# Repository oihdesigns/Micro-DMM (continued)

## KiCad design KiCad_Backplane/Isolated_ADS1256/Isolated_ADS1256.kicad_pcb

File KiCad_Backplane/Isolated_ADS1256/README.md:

# Isolated ADS1256 — rev A

This is an isolated 24-bit ADC board, 95 × 62 mm with 4 layers. The ADS1256, its reference, clock and LDOs all sit on the isolated side. SPI crosses a TI ISO7762 (5 kVrms reinforced, 4 forward / 2 reverse channels). Power crosses a Murata MEJ1S0509SC (5 V in, 9 V out, 5.2 kVDC rated, 3 pF isolation capacitance).

Status: generated, routed and checked: ERC 0, DRC 0 at all severities, 0 unconnected, schematic parity 0. It has not been ordered or tested on hardware.

## Channels

| ADS1256 inputs | Function | Scaling | Suggested setup |
|---|---|---|---|
| AIN0 / AIN1 | ±250 VDC differential | Each leg is 3 × 825k + 10k, returned to COM. k = 10k / 2.485 MΩ = 1/248.5, so 250 V gives 1.006 V. **Vin = Vdiff × 248.5** | BUFEN = 1, PGA 4: ±1.25 V full scale = ±310 V |
| AIN2 / AIN3 | 0.1 Ω shunt (RS1, TLMQ2HDR10FTE, 1.5 W) | Kelvin taps through 100 Ω, with 10 nF C0G across the pair. **I = Vdiff / 0.1** | PGA 8: ±625 mV full scale = ±6.25 A. The shunt is rated about 3.8 A continuous. |
| AIN4–7, AINCOM | Broken out on J4 | Each through 1k | — |
| D0–D3 | ADS1256 GPIOs, on J5 (3.3 V logic, isolated) | — | — |

## COM: the isolated reference (read this before connecting anything)

- **COM sits 1.5 V above GNDI.** GNDI is the ADC's own ground. U5 (OPA333) buffers COM, with 47 Ω and 10 µF on its output. This puts every input in the middle of the ADS1256 buffered input range (GNDI to AVDD−2 V, i.e. 0–3 V), so both the shunt and the divider can swing negative relative to COM.
- **COM is the node the measured circuit connects to.** JP1 is bridged by default and ties the shunt's I− end to COM. The shunt therefore defines where the isolated side sits.
- **Do not connect GNDI to the measured circuit as well.** That would short the COM buffer.
- **Common-mode limit:** each HV terminal must stay within about ±370 V of COM. The shunt must stay within about ±1.2 V of COM, which it does when JP1 is bridged.

## Connectors

- **J1 (host):** 5V, GND, VIO, ~SYNC, ~CS, DIN (MOSI), SCLK, ~DRDY, DOUT (MISO), GND.
  - VIO is your logic rail, 2.25–5.5 V.
  - 5 V input current is roughly 80 mA.
  - The isolator outputs default high, so ~CS and ~SYNC idle high when the host is off.
- **J4 (isolated analog):** A4, A5, A6, A7, AINCOM (each through 1k), COM, GNDI, 5VA (AVDD; keep the load at or below 5 mA).
- **J5 (isolated GPIO):** D0, D1, D2, D3, 3V3 (DVDD), GND.
- **J2:** HV+ / HV− screw terminal.
- **J3:** I+ / I− screw terminal.

## Firmware notes

- **~RESET** is held high by a 10k pull-up. Use the RESET command (0xFE) after power-up.
- **D0/CLKOUT** outputs 7.68 MHz after reset. Clear CLK1:0 in ADCON unless you want the clock on J5.
- **Input buffer:** use BUFEN = 1. The divider has about 10 kΩ source impedance, which is too high for the unbuffered input (about 150 kΩ / PGA).

## Isolation

- **Barrier width:** a 5.6 mm copper-free band, set by the MEJ1 module's 5.9 mm pin gap. The ISO7762 has 8 mm internally.
- **HV divider area:** no copper on In1, In2 or B.Cu underneath it. The HV netclass enforces 1.5 mm clearance on F.Cu.
- **Rating:** none of this is a certified insulation rating. Treat the board as basic insulation for a few hundred volts working, and use nylon hardware in the isolated-side mounting holes.

## Files and regenerating

- `tools/design.py` is the single source of truth.
- `tools/make_lib.py` generates `Isolated_ADS1256.kicad_sym` (ADS1256, MEJ1S0509SC, TPS7A4901).
- `tools/gen_sch.py` writes the schematic. `tools/gen_pcb.py` writes the placed, unrouted board. **Running gen_pcb wipes the routing.**
- **Routing flow** (needs a `kicad-cli api-server` running; see `tools/kipc.py`), run in this order:
  1. `stitch_planes.py`
  2. `retry.py --via` for the two LDO thermal pads
  3. `route_pass.py`
  4. `manual_ain.py`: hand-drawn AIN4–7 lanes and Kelvin taps, then +5VA and COM re-routed
  5. `post_silk.py`
  6. a manual U5 GND-to-R6 tie
- Snapshots of each stage are in `build/`.
- Output files: `Isolated_ADS1256_schematic.pdf` and `Isolated_ADS1256_BOM.csv`.

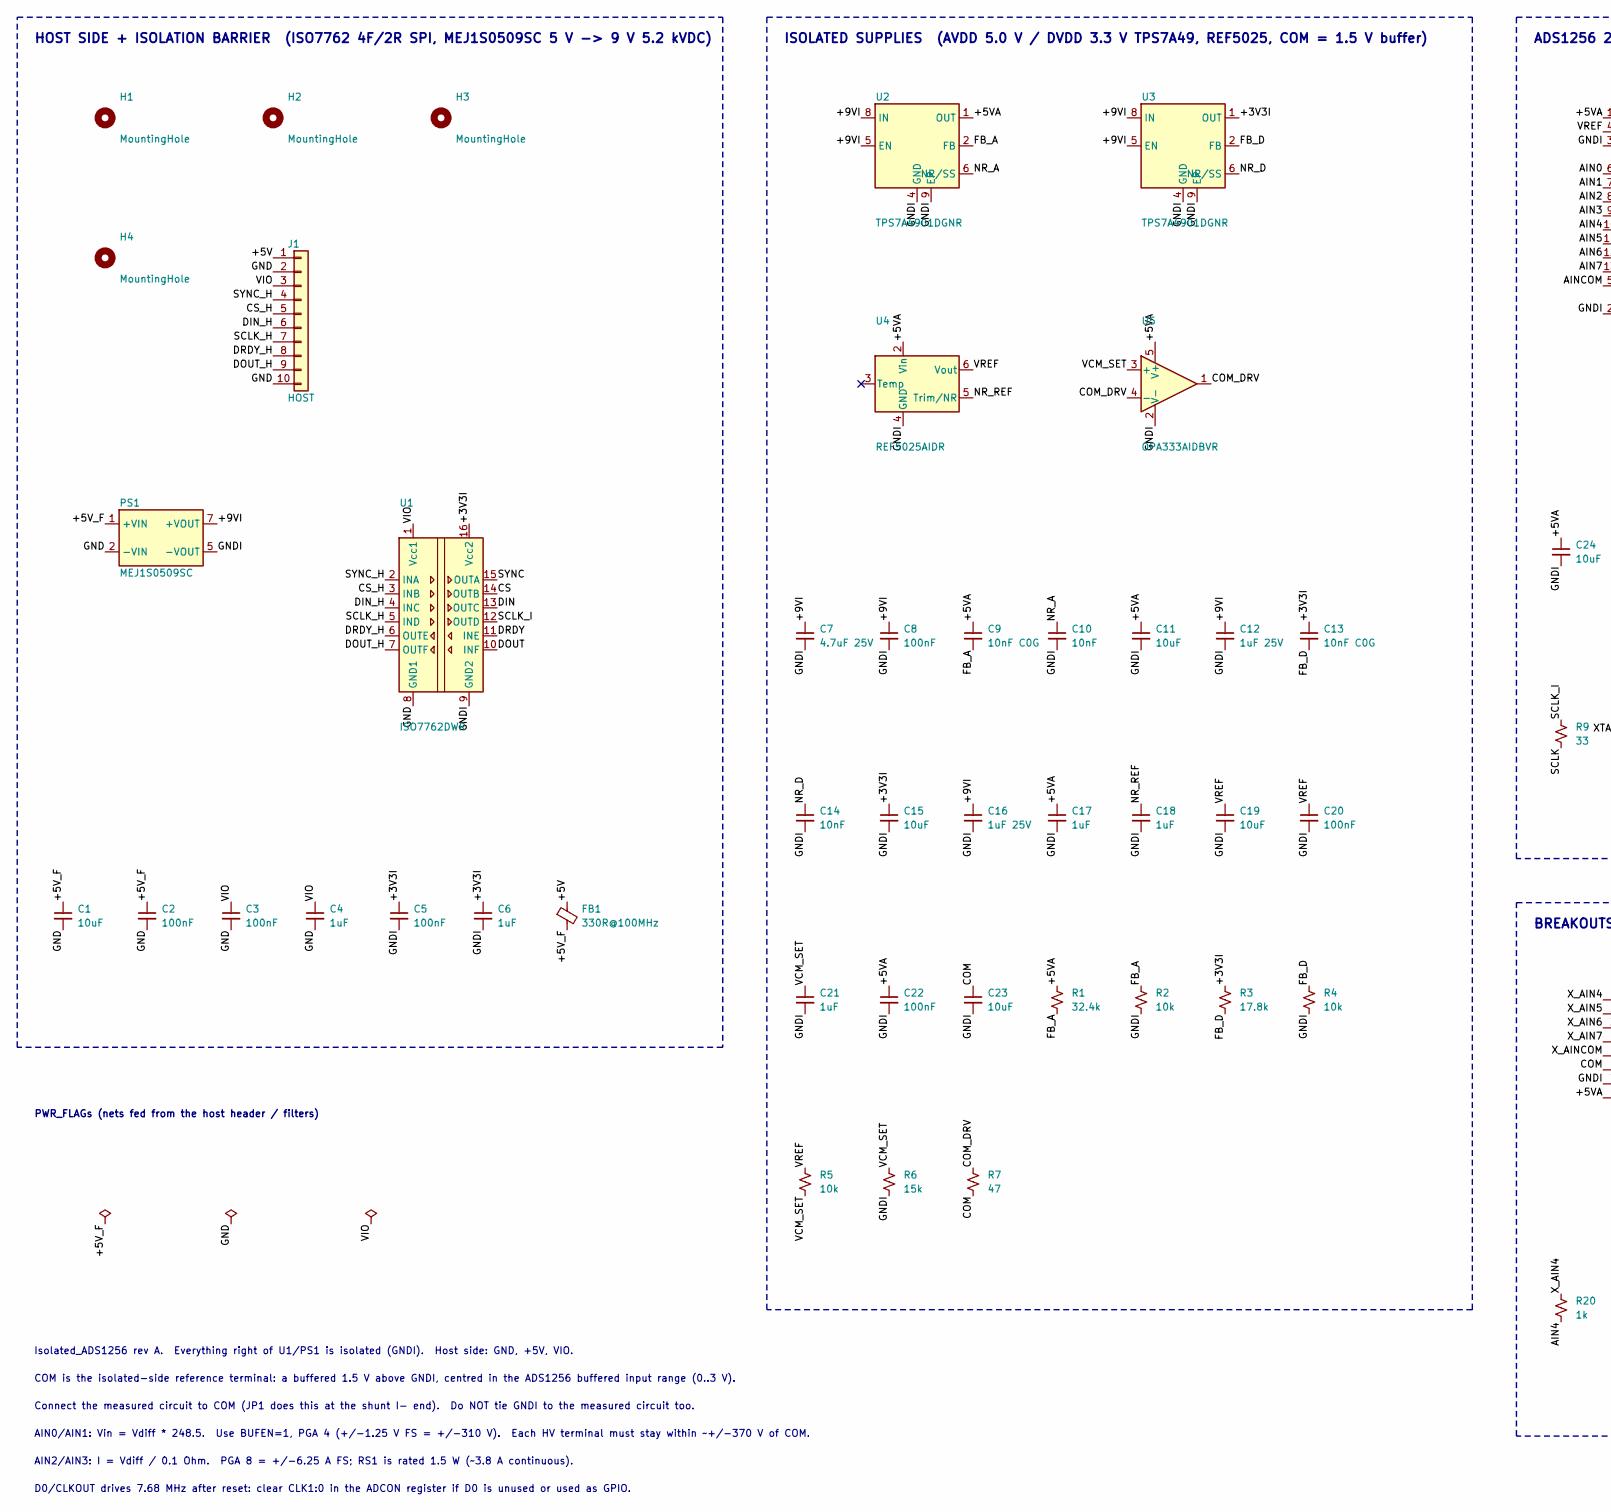
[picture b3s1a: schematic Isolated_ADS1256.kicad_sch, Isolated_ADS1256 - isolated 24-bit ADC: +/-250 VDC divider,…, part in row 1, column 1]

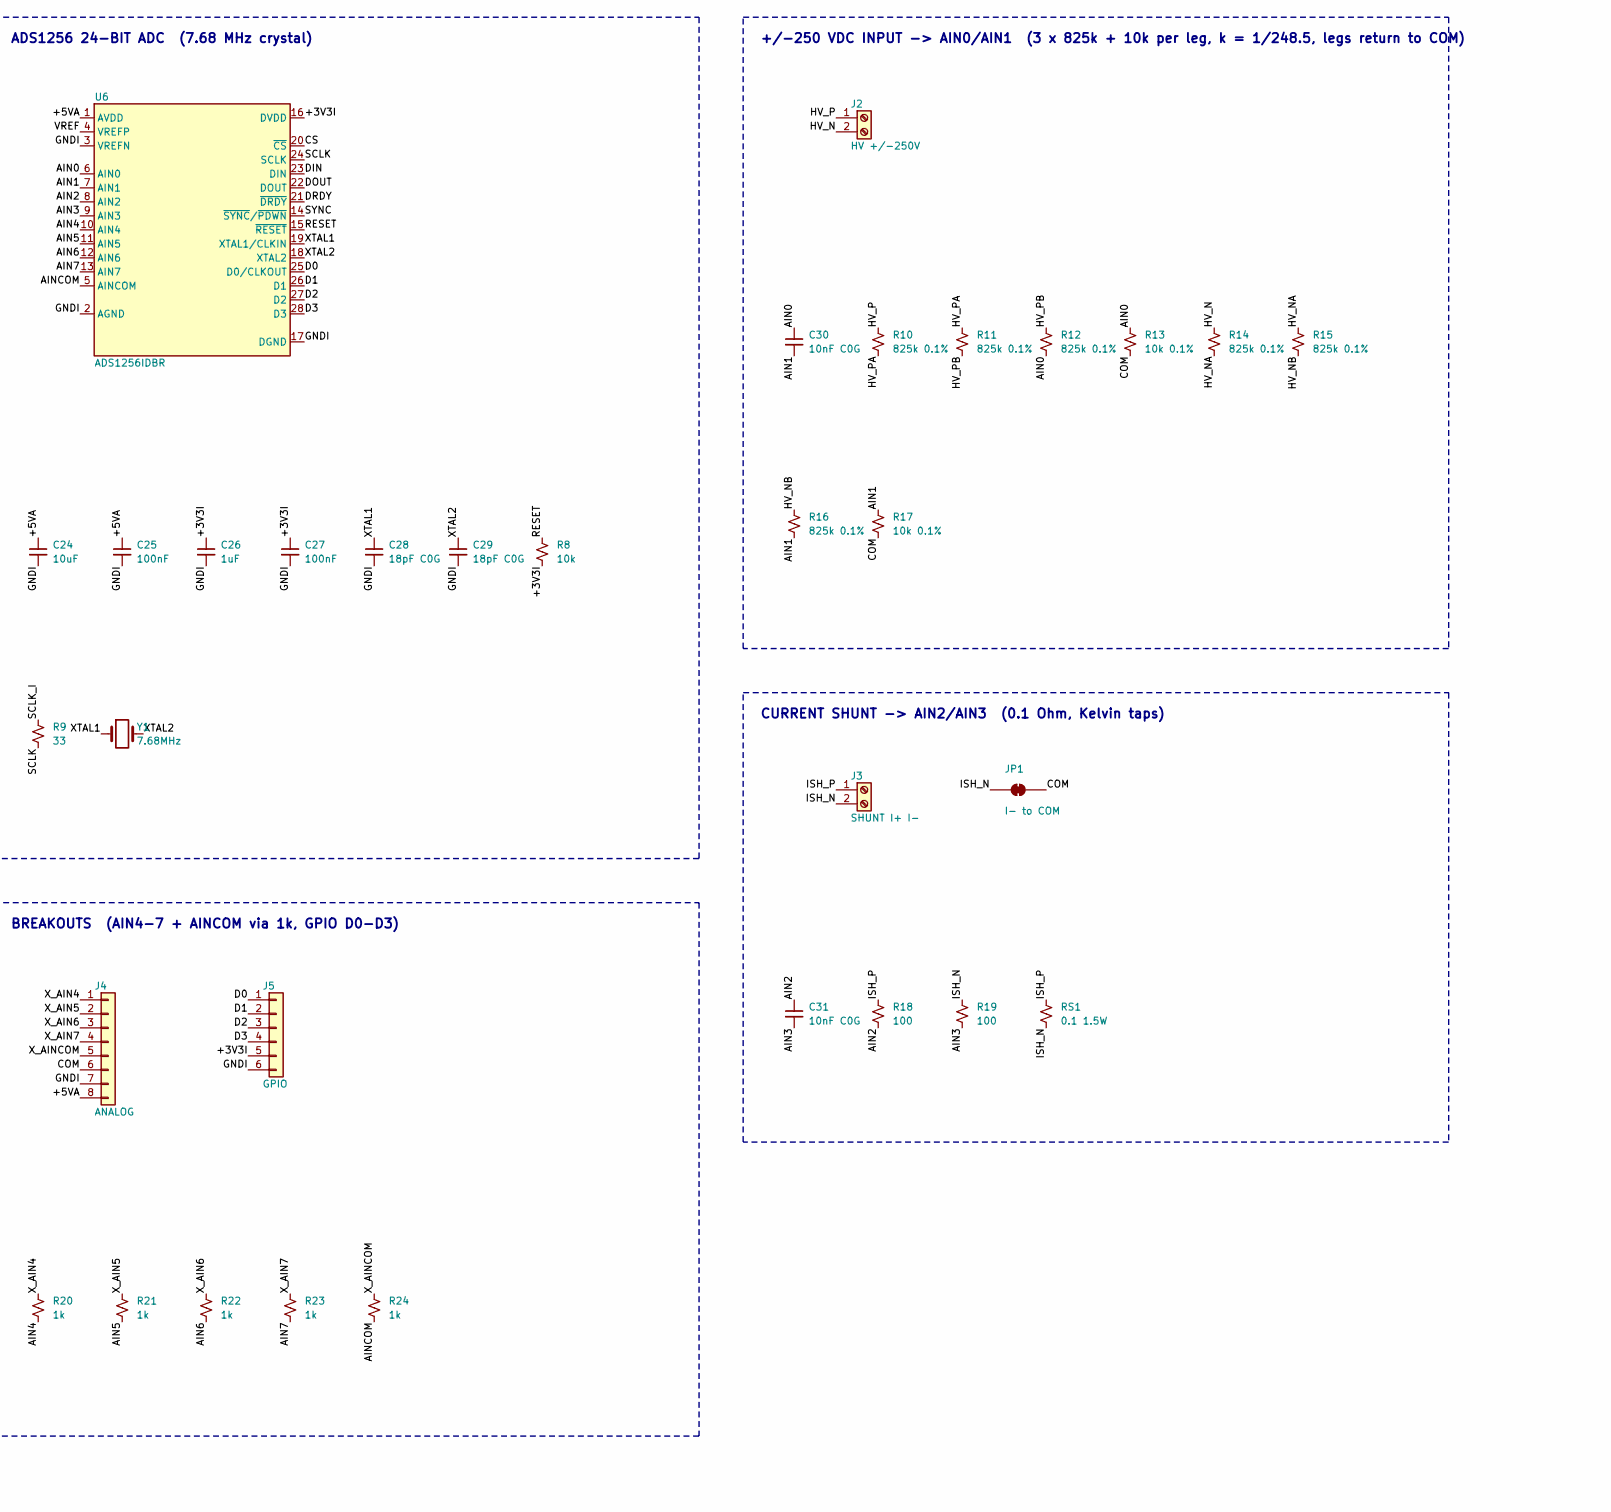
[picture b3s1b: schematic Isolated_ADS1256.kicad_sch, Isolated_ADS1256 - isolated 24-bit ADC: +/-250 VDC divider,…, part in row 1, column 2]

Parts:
C1, C11, C15, C19, C23, C24: 10uF; C_0805_2012Metric_Pad1.18x1.45mm_HandSolder
C2, C3, C5, C8, C20, C22, C25, C27: 100nF; C_0603_1608Metric_Pad1.08x0.95mm_HandSolder
C4, C6, C17, C18, C21, C26: 1uF; C_0603_1608Metric_Pad1.08x0.95mm_HandSolder
C7: 4.7uF 25V; C_0805_2012Metric_Pad1.18x1.45mm_HandSolder
C9, C13: 10nF C0G; C_0603_1608Metric_Pad1.08x0.95mm_HandSolder
C10, C14: 10nF; C_0603_1608Metric_Pad1.08x0.95mm_HandSolder
C12, C16: 1uF 25V; C_0603_1608Metric_Pad1.08x0.95mm_HandSolder
C28, C29: 18pF C0G; C_0603_1608Metric_Pad1.08x0.95mm_HandSolder
C30, C31: 10nF C0G; C_0805_2012Metric_Pad1.18x1.45mm_HandSolder
FB1: 330R@100MHz; L_0805_2012Metric_Pad1.05x1.20mm_HandSolder
H1, H2, H3, H4: MountingHole; MountingHole_3.2mm_M3
J1: HOST; PinHeader_1x10_P2.54mm_Vertical
J2: HV +/-250V; TerminalBlock_RND_205-00232_1x02_P5.08mm_Horizontal
J3: SHUNT I+ I-; TerminalBlock_RND_205-00232_1x02_P5.08mm_Horizontal
J4: ANALOG; PinHeader_1x08_P2.54mm_Vertical
J5: GPIO; PinHeader_1x06_P2.54mm_Vertical
JP1: I- to COM; SolderJumper-2_P1.3mm_Bridged_RoundedPad1.0x1.5mm
PS1: MEJ1S0509SC; Converter_DCDC_muRata_MEJ1SxxxxSC_THT
R1: 32.4k; R_0603_1608Metric_Pad0.98x0.95mm_HandSolder
R2, R4, R5, R8: 10k; R_0603_1608Metric_Pad0.98x0.95mm_HandSolder
R3: 17.8k; R_0603_1608Metric_Pad0.98x0.95mm_HandSolder
R6: 15k; R_0603_1608Metric_Pad0.98x0.95mm_HandSolder
R7: 47; R_0603_1608Metric_Pad0.98x0.95mm_HandSolder
R9: 33; R_0603_1608Metric_Pad0.98x0.95mm_HandSolder
R10, R11, R12, R14, R15, R16: 825k 0.1%; R_1206_3216Metric_Pad1.30x1.75mm_HandSolder
R13, R17: 10k 0.1%; R_0805_2012Metric_Pad1.20x1.40mm_HandSolder
R18, R19: 100; R_0603_1608Metric_Pad0.98x0.95mm_HandSolder
R20, R21, R22, R23, R24: 1k; R_0603_1608Metric_Pad0.98x0.95mm_HandSolder
RS1: 0.1 1.5W; R_2010_5025Metric_Pad1.40x2.65mm_HandSolder
U1: ISO7762DWR; SOIC-16W_7.5x10.3mm_P1.27mm
U2, U3: TPS7A4901DGNR; HVSSOP-8-1EP_3x3mm_P0.65mm_EP1.57x1.89mm
U4: REF5025AIDR; SOIC-8_3.9x4.9mm_P1.27mm
U5: OPA333AIDBVR; SOT-23-5
U6: ADS1256IDBR; SSOP-28_5.3x10.2mm_P0.65mm
Y1: 7.68MHz; Crystal_SMD_HC49-SD

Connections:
/+3V3I: C5.1, C6.1, C13.1, C15.1, C26.1, C27.1, J5.5, R3.1, R8.2, U1.16 (Vcc2), U3.1 (OUT), U6.16 (DVDD)
/+5V: FB1.1, J1.1
/+5VA: C9.1, C11.1, C17.1, C22.1, C24.1, C25.1, J4.8, R1.1, U2.1 (OUT), U4.2 (Vin), U5.5 (V+), U6.1 (AVDD)
/+5V_F: C1.1, C2.1, FB1.2, PS1.1 (+VIN)
/+9VI: C7.1, C8.1, C12.1, C16.1, PS1.7 (+VOUT), U2.5 (EN), U2.8 (IN), U3.5 (EN), U3.8 (IN)
/AIN0: C30.1, R12.2, R13.1, U6.6 (AIN0)
/AIN1: C30.2, R16.2, R17.1, U6.7 (AIN1)
/AIN2: C31.1, R18.2, U6.8 (AIN2)
/AIN3: C31.2, R19.2, U6.9 (AIN3)
/AIN4: R20.2, U6.10 (AIN4)
/AIN5: R21.2, U6.11 (AIN5)
/AIN6: R22.2, U6.12 (AIN6)
/AIN7: R23.2, U6.13 (AIN7)
/AINCOM: R24.2, U6.5 (AINCOM)
/COM: C23.1, J4.6, JP1.2 (B), R7.2, R13.2, R17.2
/COM_DRV: R7.1, U5.1, U5.4 (-)
/CS: U1.14 (OUTB), U6.20 (~CS)
/CS_H: J1.5, U1.3 (INB)
/D0: J5.1, U6.25 (D0/CLKOUT)
/D1: J5.2, U6.26 (D1)
/D2: J5.3, U6.27 (D2)
/D3: J5.4, U6.28 (D3)
/DIN: U1.13 (OUTC), U6.23 (DIN)
/DIN_H: J1.6, U1.4 (INC)
/DOUT: U1.10 (INF), U6.22 (DOUT)
/DOUT_H: J1.9, U1.7 (OUTF)
/DRDY: U1.11 (INE), U6.21 (~DRDY)
/DRDY_H: J1.8, U1.6 (OUTE)
/FB_A: C9.2, R1.2, R2.1, U2.2 (FB)
/FB_D: C13.2, R3.2, R4.1, U3.2 (FB)
/GND: C1.2, C2.2, C3.2, C4.2, J1.2, J1.10, PS1.2 (-VIN), U1.8 (GND1)
/GNDI: C5.2, C6.2, C7.2, C8.2, C10.2, C11.2, C12.2, C14.2, C15.2, C16.2, C17.2, C18.2, C19.2, C20.2, C21.2, C22.2, C23.2, C24.2, C25.2, C26.2, C27.2, C28.2, C29.2, J4.7, J5.6, PS1.5 (-VOUT), R2.2, R4.2, R6.2, U1.9 (GND2), U2.4 (GND), U2.9 (EP), U3.4 (GND), U3.9 (EP), U4.4 (GND), U5.2 (V-), U6.2 (AGND), U6.3 (VREFN), U6.17 (DGND)
/HV_N: J2.2, R14.1
/HV_NA: R14.2, R15.1
/HV_NB: R15.2, R16.1
/HV_P: J2.1, R10.1
/HV_PA: R10.2, R11.1
/HV_PB: R11.2, R12.1
/ISH_N: J3.2, JP1.1 (A), R19.1, RS1.2
/ISH_P: J3.1, R18.1, RS1.1
/NR_A: C10.1, U2.6 (NR/SS)
/NR_D: C14.1, U3.6 (NR/SS)
/NR_REF: C18.1, U4.5 (Trim/NR)
/RESET: R8.1, U6.15 (~RESET)
/SCLK: R9.2, U6.24 (SCLK)
/SCLK_H: J1.7, U1.5 (IND)
/SCLK_I: R9.1, U1.12 (OUTD)
/SYNC: U1.15 (OUTA), U6.14 (~SYNC/~PDWN)
/SYNC_H: J1.4, U1.2 (INA)
/VCM_SET: C21.1, R5.2, R6.1, U5.3 (+)
/VIO: C3.1, C4.1, J1.3, U1.1 (Vcc1)
/VREF: C19.1, C20.1, R5.1, U4.6 (Vout), U6.4 (VREFP)
/XTAL1: C28.1, U6.19 (XTAL1/CLKIN), Y1.1
/XTAL2: C29.1, U6.18 (XTAL2), Y1.2
/X_AIN4: J4.1, R20.1
/X_AIN5: J4.2, R21.1
/X_AIN6: J4.3, R22.1
/X_AIN7: J4.4, R23.1
/X_AINCOM: J4.5, R24.1

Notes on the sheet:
HOST SIDE + ISOLATION BARRIER (ISO7762 4F/2R SPI, MEJ1S0509SC 5 V -> 9 V 5.2 kVDC)
ISOLATED SUPPLIES (AVDD 5.0 V / DVDD 3.3 V TPS7A49, REF5025, COM = 1.5 V buffer)
ADS1256 24-BIT ADC (7.68 MHz crystal)
BREAKOUTS (AIN4-7 + AINCOM via 1k, GPIO D0-D3)
+/-250 VDC INPUT -> AIN0/AIN1 (3 x 825k + 10k per leg, k = 1/248.5, legs return to COM)
CURRENT SHUNT -> AIN2/AIN3 (0.1 Ohm, Kelvin taps)
PWR_FLAGs (nets fed from the host header / filters)
Isolated_ADS1256 rev A. Everything right of U1/PS1 is isolated (GNDI). Host side: GND, +5V, VIO.
COM is the isolated-side reference terminal: a buffered 1.5 V above GNDI, centred in the ADS1256 buffered input range (0..3 V).
Connect the measured circuit to COM (JP1 does this at the shunt I- end). Do NOT tie GNDI to the measured circuit too.
AIN0/AIN1: Vin = Vdiff * 248.5. Use BUFEN=1, PGA 4 (+/-1.25 V FS = +/-310 V). Each HV terminal must stay within ~+/-370 V of COM.
AIN2/AIN3: I = Vdiff / 0.1 Ohm. PGA 8 = +/-6.25 A FS; RS1 is rated 1.5 W (~3.8 A continuous).
D0/CLKOUT drives 7.68 MHz after reset: clear CLK1:0 in the ADCON register if D0 is unused or used as GPIO.

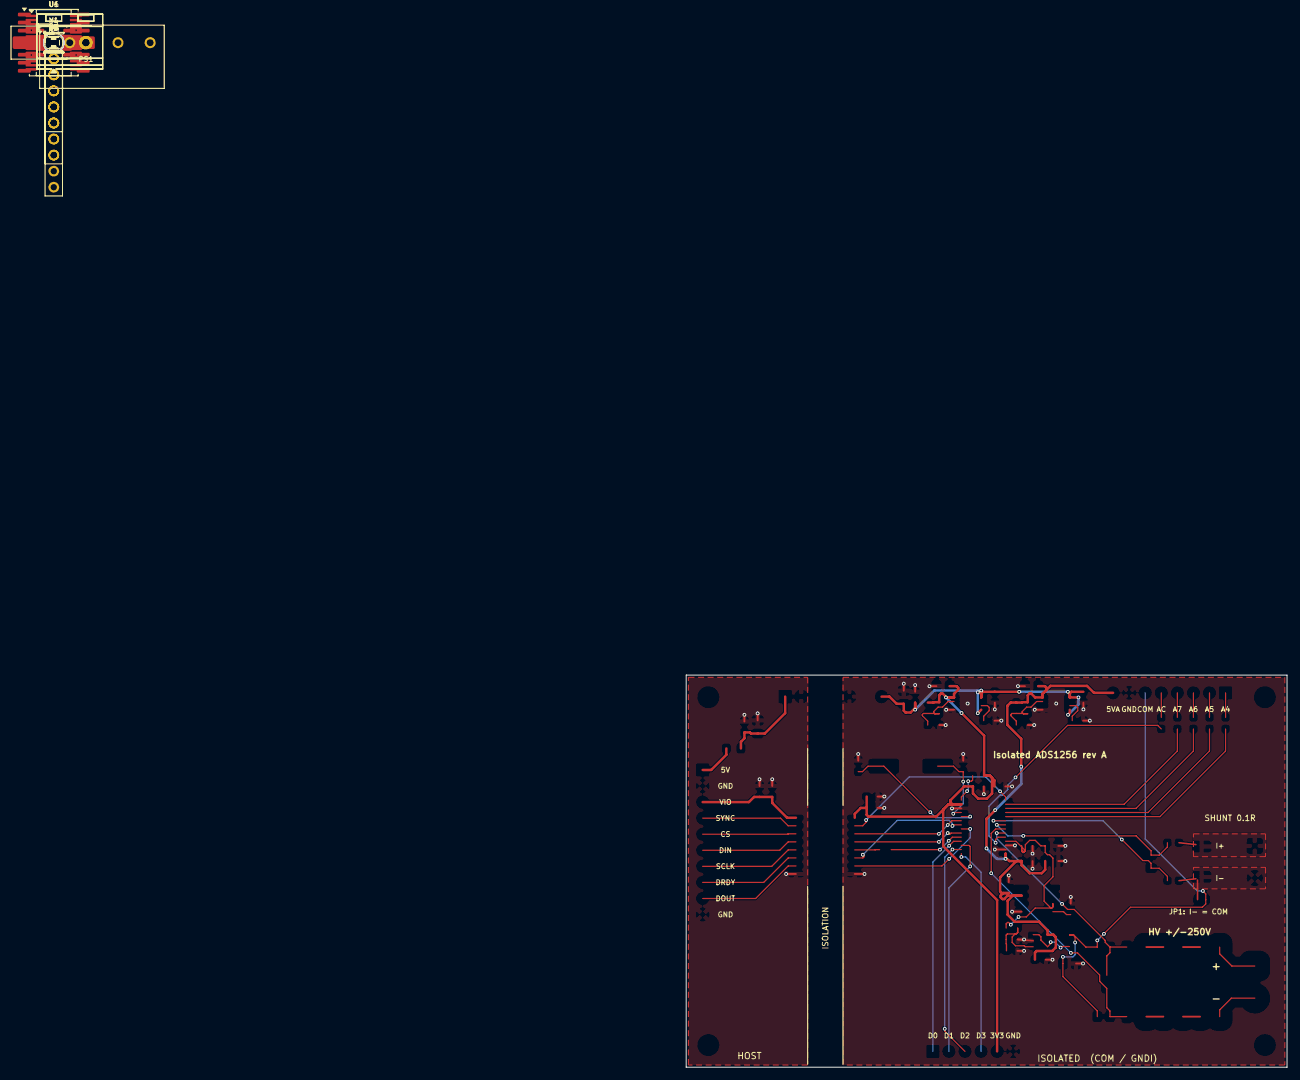
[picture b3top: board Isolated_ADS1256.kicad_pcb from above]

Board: 4 copper layers, 95.0 x 62.0 mm, 75 parts (0 on the bottom side), 59 nets.

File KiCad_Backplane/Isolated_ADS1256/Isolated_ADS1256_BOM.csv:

"Reference","Value","Footprint","PN","QUANTITY","DNP"
"C1,C11,C15,C19,C23,C24","10uF","Capacitor_SMD:C_0805_2012Metric_Pad1.18x1.45mm_HandSolder","GRM21BR61E106KA73L","6",""
"C2,C3,C5,C8,C20,C22,C25,C27","100nF","Capacitor_SMD:C_0603_1608Metric_Pad1.08x0.95mm_HandSolder","GRM188R71H104KA93D","8",""
"C4,C6,C17,C18,C21,C26","1uF","Capacitor_SMD:C_0603_1608Metric_Pad1.08x0.95mm_HandSolder","GRM188R61E105KA12D","6",""
"C7","4.7uF 25V","Capacitor_SMD:C_0805_2012Metric_Pad1.18x1.45mm_HandSolder","GRM21BR61E475KA12L","1",""
"C9,C13","10nF C0G","Capacitor_SMD:C_0603_1608Metric_Pad1.08x0.95mm_HandSolder","GRM1885C1H103JA01D","2",""
"C10,C14","10nF","Capacitor_SMD:C_0603_1608Metric_Pad1.08x0.95mm_HandSolder","GRM188R71H103KA01D","2",""
"C12,C16","1uF 25V","Capacitor_SMD:C_0603_1608Metric_Pad1.08x0.95mm_HandSolder","GRM188R61E105KA12D","2",""
"C28,C29","18pF C0G","Capacitor_SMD:C_0603_1608Metric_Pad1.08x0.95mm_HandSolder","GRM1885C1H180JA01D","2",""
"C30,C31","10nF C0G","Capacitor_SMD:C_0805_2012Metric_Pad1.18x1.45mm_HandSolder","GRM2195C1H103JA01D","2",""
"FB1","330R@100MHz","Inductor_SMD:L_0805_2012Metric_Pad1.05x1.20mm_HandSolder","BLM21PG331SN1D","1",""
"J1","HOST","Connector_PinHeader_2.54mm:PinHeader_1x10_P2.54mm_Vertical","PH1-10-UA","1",""
"J2","HV +/-250V","TerminalBlock_RND:TerminalBlock_RND_205-00232_1x02_P5.08mm_Horizontal","TBJ05-02-1-G-G","1",""
"J3","SHUNT I+ I-","TerminalBlock_RND:TerminalBlock_RND_205-00232_1x02_P5.08mm_Horizontal","TBJ05-02-1-G-G","1",""
"J4","ANALOG","Connector_PinHeader_2.54mm:PinHeader_1x08_P2.54mm_Vertical","PH1-08-UA","1",""
"J5","GPIO","Connector_PinHeader_2.54mm:PinHeader_1x06_P2.54mm_Vertical","PH1-06-UA","1",""
"PS1","MEJ1S0509SC","Converter_DCDC:Converter_DCDC_muRata_MEJ1SxxxxSC_THT","MEJ1S0509SC","1",""
"R1","32.4k","Resistor_SMD:R_0603_1608Metric_Pad0.98x0.95mm_HandSolder","ERJ-3EKF3242V","1",""
"R2,R4,R5,R8","10k","Resistor_SMD:R_0603_1608Metric_Pad0.98x0.95mm_HandSolder","ERJ-3EKF1002V","4",""
"R3","17.8k","Resistor_SMD:R_0603_1608Metric_Pad0.98x0.95mm_HandSolder","ERJ-3EKF1782V","1",""
"R6","15k","Resistor_SMD:R_0603_1608Metric_Pad0.98x0.95mm_HandSolder","ERJ-3EKF1502V","1",""
"R7","47","Resistor_SMD:R_0603_1608Metric_Pad0.98x0.95mm_HandSolder","ERJ-3EKF47R0V","1",""
"R9","33","Resistor_SMD:R_0603_1608Metric_Pad0.98x0.95mm_HandSolder","ERJ-3EKF33R0V","1",""
"R10-R12,R14-R16","825k 0.1%","Resistor_SMD:R_1206_3216Metric_Pad1.30x1.75mm_HandSolder","ERA-8AEB8253V","6",""
"R13,R17","10k 0.1%","Resistor_SMD:R_0805_2012Metric_Pad1.20x1.40mm_HandSolder","ERA-6AEB103V","2",""
"R18,R19","100","Resistor_SMD:R_0603_1608Metric_Pad0.98x0.95mm_HandSolder","ERA-3AEB101V","2",""
"R20-R24","1k","Resistor_SMD:R_0603_1608Metric_Pad0.98x0.95mm_HandSolder","ERJ-3EKF1001V","5",""
"RS1","0.1 1.5W","Resistor_SMD:R_2010_5025Metric_Pad1.40x2.65mm_HandSolder","TLMQ2HDR10FTE","1",""
"U1","ISO7762DWR","Package_SO:SOIC-16W_7.5x10.3mm_P1.27mm","ISO7762DWR","1",""
"U2,U3","TPS7A4901DGNR","Package_SO:HVSSOP-8-1EP_3x3mm_P0.65mm_EP1.57x1.89mm","TPS7A4901DGNR","2",""
"U4","REF5025AIDR","Package_SO:SOIC-8_3.9x4.9mm_P1.27mm","REF5025AIDR","1",""
"U5","OPA333AIDBVR","Package_TO_SOT_SMD:SOT-23-5","OPA333AIDBVR","1",""
"U6","ADS1256IDBR","Package_SO:SSOP-28_5.3x10.2mm_P0.65mm","ADS1256IDBR","1",""
"Y1","7.68MHz","Crystal:Crystal_SMD_HC49-SD","ECS-76.8-18-5PXEN-TR","1",""

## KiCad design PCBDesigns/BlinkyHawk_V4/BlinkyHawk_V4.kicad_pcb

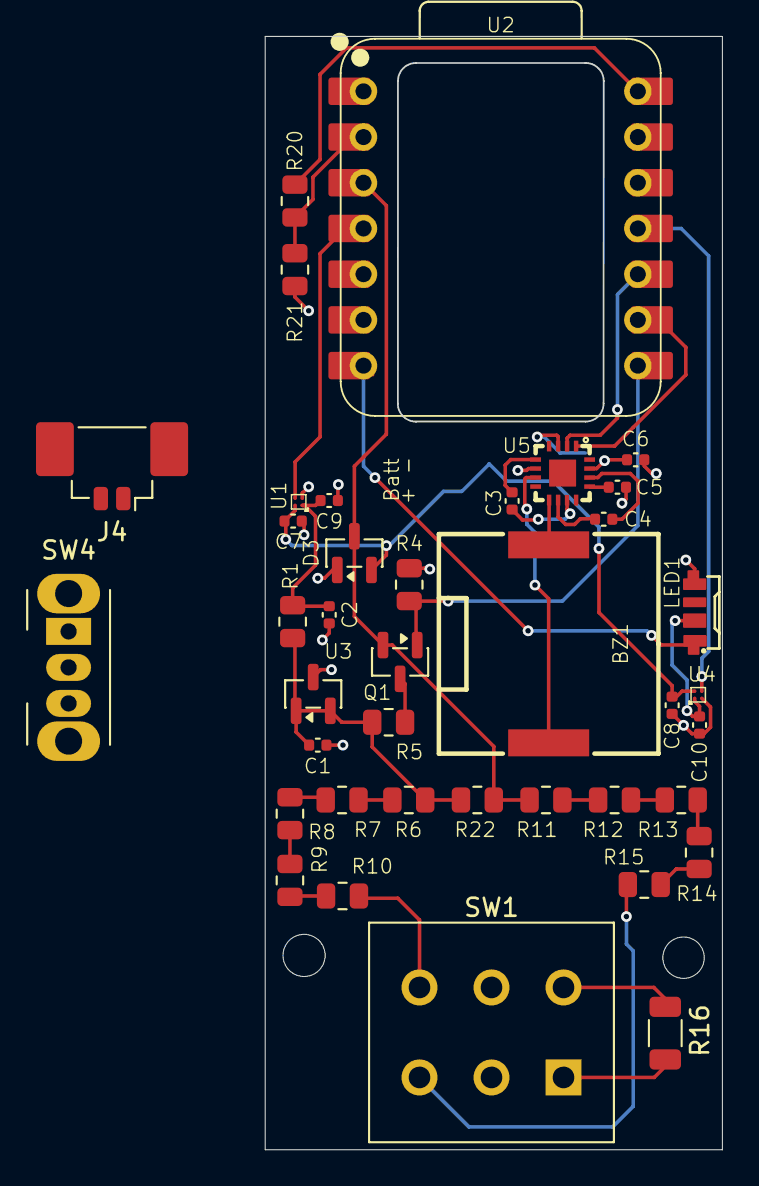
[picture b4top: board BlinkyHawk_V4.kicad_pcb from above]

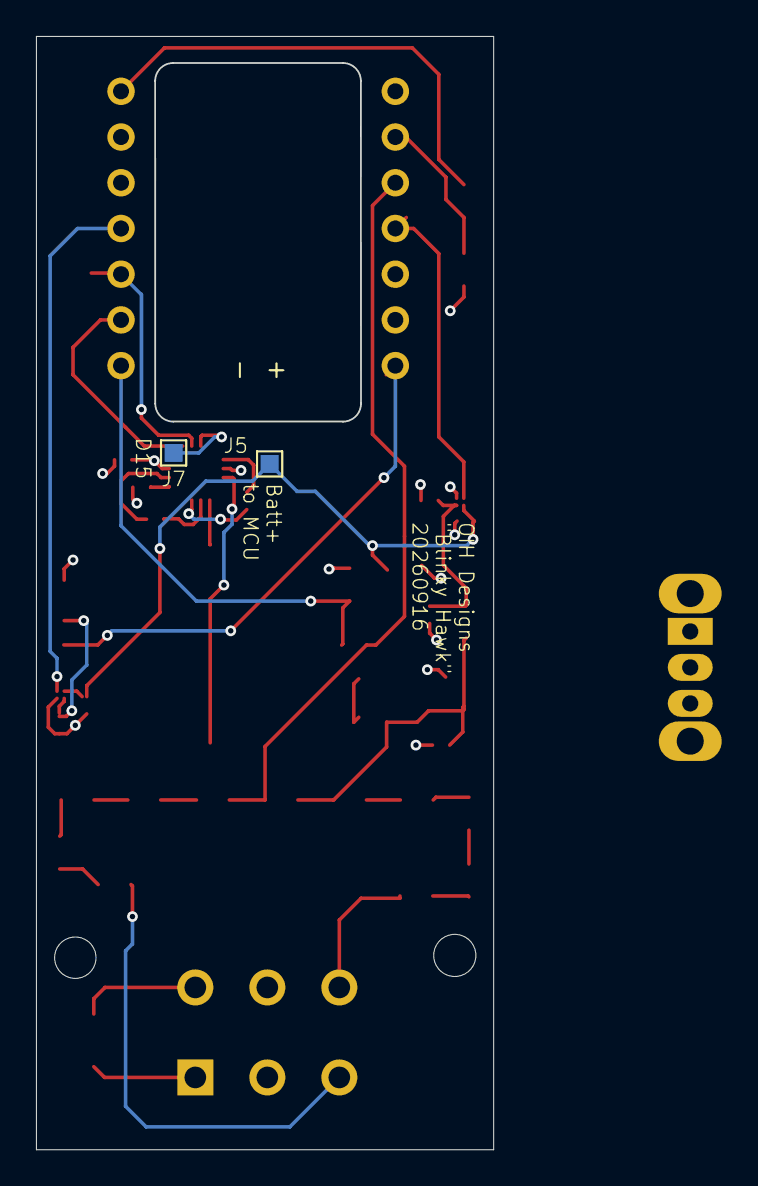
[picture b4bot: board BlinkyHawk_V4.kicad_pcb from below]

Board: 4 copper layers, 25.4 x 61.8 mm, 41 parts (2 on the bottom side), 37 nets.

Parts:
BZ1: Buzzer; BUZ-SMD_2P-L12.0-W12.0-L_PKLCS1212E4001-R1
C1, C9, C10: 0.1uF; C_0402_1005Metric
C2, C3, C4, C7, C8: 1uF; C_0402_1005Metric
C5, C6: 2.2uF; C_0402_1005Metric
D3: BAT54S; SOT-23
J4: Battery; Molex_PicoBlade_53398-0271_1x02-1MP_P1.25mm_Vertical
J5, J7: Conn_01x01; TestPoint_Pad_1.0x1.0mm
LED1: SK6812SIDE-A_C5378721; LED-SMD_4P-L4.0-W1.6-L
Q1: AO3400A MOSFET; SOT-23
R1: 4.7K; R_0805_2012Metric
R4, R5, R6, R7, R8, R9, R10, R11, R12, R13, R14, R15, R20, R21: 100K; R_0805_2012Metric
R16: 100K; R_1206_3216Metric
R22: 1Meg; R_0805_2012Metric
SW1: SW_Push_DPDT; SW_PUSH_E-Switch_FS5700DP_DPDT
SW4: SW_SPDT; SW_Slide_SPDT_Angled_CK_OS102011MA1Q
U1, U4: TPS22914BYFPR; DSBGA-4_L0.8-W0.8-R2-C2-P0.40-BL
U2: XIAO-R4-DIP
U3: TL431DBZ; SOT-23
U5: PAM8904JER; TQFN-16_L3.0-W3.0-P0.50-BL-EP1.5

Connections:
5vRail: C7.1, C8.1, D3.2 (K), R20.2, U1.A2 (VIN), U2.14 (5V), U4.A2 (VIN)
+3V3: C6.1, U2.12 (3V3), U5.15 (VIN)
A1: R20.1, R21.1, U2.2 (PA4_A1_D1)
A2: D3.3 (COM), Q1.2 (S), R11.2, R22.2, U2.3 (PA10_A2_D2)
A3: U1.B2 (ON), U2.4 (PA11_A3_D3)
Analog_Rail: C2.2, C9.2, R1.1, U1.A1 (VOUT)
Bridge_CRTL: Q1.1 (G), R4.2, U2.8 (PB09_A7_D7_RX)
D6: LED1.1 (DIN), U2.7 (PB08_A6_D6_TX)
D8: U2.9 (PA7_A8_D8_SCK), U5.1 (EN1)
D9: U2.10 (PA5_A9_D9_MISO), U5.2 (EN2)
D10: U2.11 (PA6_A10_D10_MOSI), U4.B2 (ON)
D15: J7.1 (Pin_1_1), U5.3 (DIN)
Gnd: C1.1, C2.1, C5.2, C6.2, C7.2, C8.2, C9.1, C10.1, D3.1 (A), J4.1, LED1.4 (GND), R4.1, R21.2, U1.B1 (GND), U2.13 (GND), U3.3 (A), U4.B1 (GND), U5.6 (GND)
LEDRail: C10.2, LED1.2 (VDD), U4.A1 (VOUT)
unnamed: BZ1.1 (+), U5.9 (VO1)
unnamed: BZ1.2 (-), U5.7 (VO2)
unnamed: J4.2, SW4.1 (A)
unnamed: J5.1 (Pin_1_1), SW4.2 (B)
unnamed: Q1.3 (D), R5.1
unnamed: R6.1, R7.2
unnamed: R7.1, R8.2
unnamed: R8.1, R9.2
unnamed: R9.1, R10.2
unnamed: R11.1, R12.2
unnamed: R12.1, R13.2
unnamed: R13.1, R14.2
unnamed: R14.1, R15.2
unnamed: R16.1, SW1.1 (A)
unnamed: R16.2, SW1.4 (A)
unnamed: C1.2, R1.2, R5.2, R6.2, R22.1, U3.1 (K), U3.2 (REF)
unnamed: C3.2, U5.5 (CN1)
unnamed: C4.2, U5.10 (CN2)
unnamed: C3.1, U5.11 (CP1)
unnamed: C4.1, U5.14 (CP2)
unnamed: C5.1, U5.13 (VOUT)
V_Input_Float: R15.1, SW1.3 (C)
V_Input_REF: R10.1, SW1.6 (C)
